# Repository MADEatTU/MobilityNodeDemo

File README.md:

# Mobility Node Demo
Proof of concept for CAN-bus connected mobility project modules.

This is a minimally viable circuit to prototype firmware and electrical designs communicating over CAN bus. Each board has one LED and three push buttons, allowing both targeted and global message passing to be tested. Boards are capable of daisy-chaining.

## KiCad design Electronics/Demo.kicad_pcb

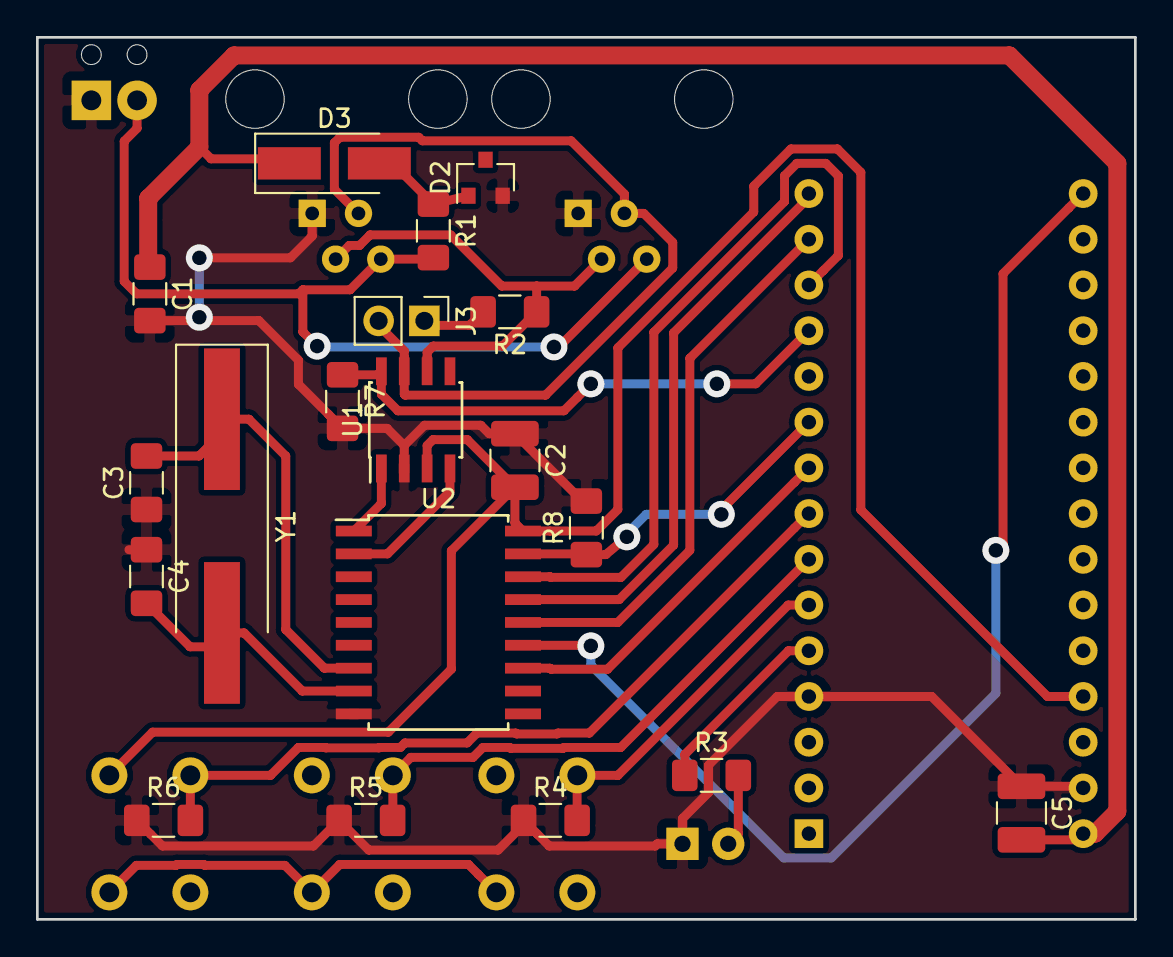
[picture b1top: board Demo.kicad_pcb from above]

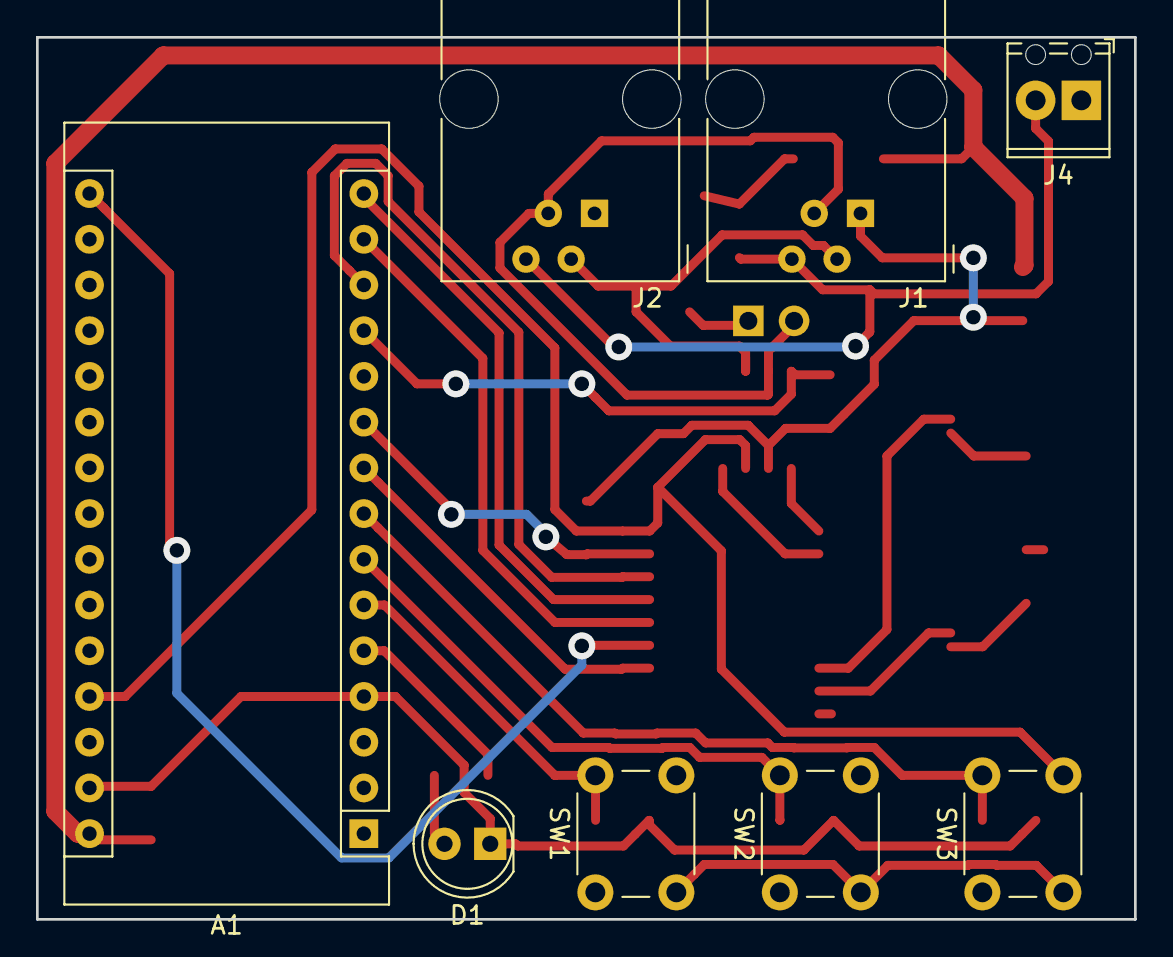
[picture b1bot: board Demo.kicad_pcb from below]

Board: 2 copper layers, 61.0 x 49.0 mm, 27 parts (8 on the bottom side), 24 nets.

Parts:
A1: Arduino_Nano_v3.x; Arduino_Nano
C1: 1uF; C_1206_3216Metric_Pad1.42x1.75mm_HandSolder
C2, C5: 0.1uF; C_1210_3225Metric_Pad1.42x2.65mm_HandSolder
C3, C4: 22pF; C_1206_3216Metric_Pad1.42x1.75mm_HandSolder
D1: LED; LED_D5.0mm
D2: 12V; SOT-23
D3: D_Schottky; D_SMA_Handsoldering
J1, J2: RJ10; RJ14
J3: Conn_01x02_Male; PinHeader_1x02_P2.54mm_Vertical
J4: PWR; TerminalBlock_Phoenix_MPT-0,5-2-2.54_1x02_P2.54mm_Horizontal
R1: 6.8; R_1206_3216Metric_Pad1.42x1.75mm_HandSolder
R2: 100; R_1206_3216Metric_Pad1.42x1.75mm_HandSolder
R3, R4, R5, R6: 1k; R_1206_3216Metric_Pad1.42x1.75mm_HandSolder
R7, R8: 22k; R_1206_3216Metric_Pad1.42x1.75mm_HandSolder
SW1, SW2, SW3: SW_Push; SW_PUSH_6mm_H4.3mm
U1: MCP2551-I-SN; SOIC-8_3.9x4.9mm_P1.27mm
U2: MCP2515-xSO; SOIC-18W_7.5x11.6mm_P1.27mm
Y1: 8MHz; Crystal_SMD_HC49-SD_HandSoldering

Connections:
+5V: A1.27, C2.2, SW1.2, SW2.2, SW3.2, U1.3, U2.18
+12V: A1.30, C1.1, C5.2, D3.1
/CANH: J1.3, J2.3, J3.2, U1.7
/CANL: J1.2, J2.2, R2.1, U1.6
/CAN_RST: A1.10, R8.1, U2.17
/CS: A1.13, U2.16
/LED: A1.5, R3.1
/RXD: U1.4, U2.2
/S1: A1.6, R4.2, SW1.1
/S2: A1.7, R5.2, SW2.1
/S3: A1.8, R6.2, SW3.1
/SCK: A1.16, U2.13
/SI: A1.14, U2.14
/SO: A1.15, U2.15
/TXD: U1.1, U2.1
/Vin: J1.4, J2.4, J4.2, R1.2
/XCDR_RST: A1.12, R7.1, U1.8
/int: A1.9, U2.12
GND: A1.4, A1.29, C1.2, C2.1, C3.1, C4.1, C5.1, D1.1, D2.2, J1.1, J2.1, J4.1, R4.1, R5.1, R6.1, R7.2, R8.2, U1.2, U2.9
unnamed: C3.2, U2.7, Y1.1
unnamed: C4.2, U2.8, Y1.2
unnamed: D1.2, R3.2
unnamed: D2.1, D3.2, R1.1
unnamed: J3.1, R2.2

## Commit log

2019-01-04 Initial commit.
2019-01-05 Updated gcode.
2019-01-05 UPdated edge
2019-01-06 Included power in screw terminal
2019-01-06 Corrected mismatched offsets
2019-01-15 Updated footprints and routing.
2019-01-18 Duplicate work.
2019-01-19 Corrected footprint and tuned traces.
2019-01-21 Generated new manufacturing files.
